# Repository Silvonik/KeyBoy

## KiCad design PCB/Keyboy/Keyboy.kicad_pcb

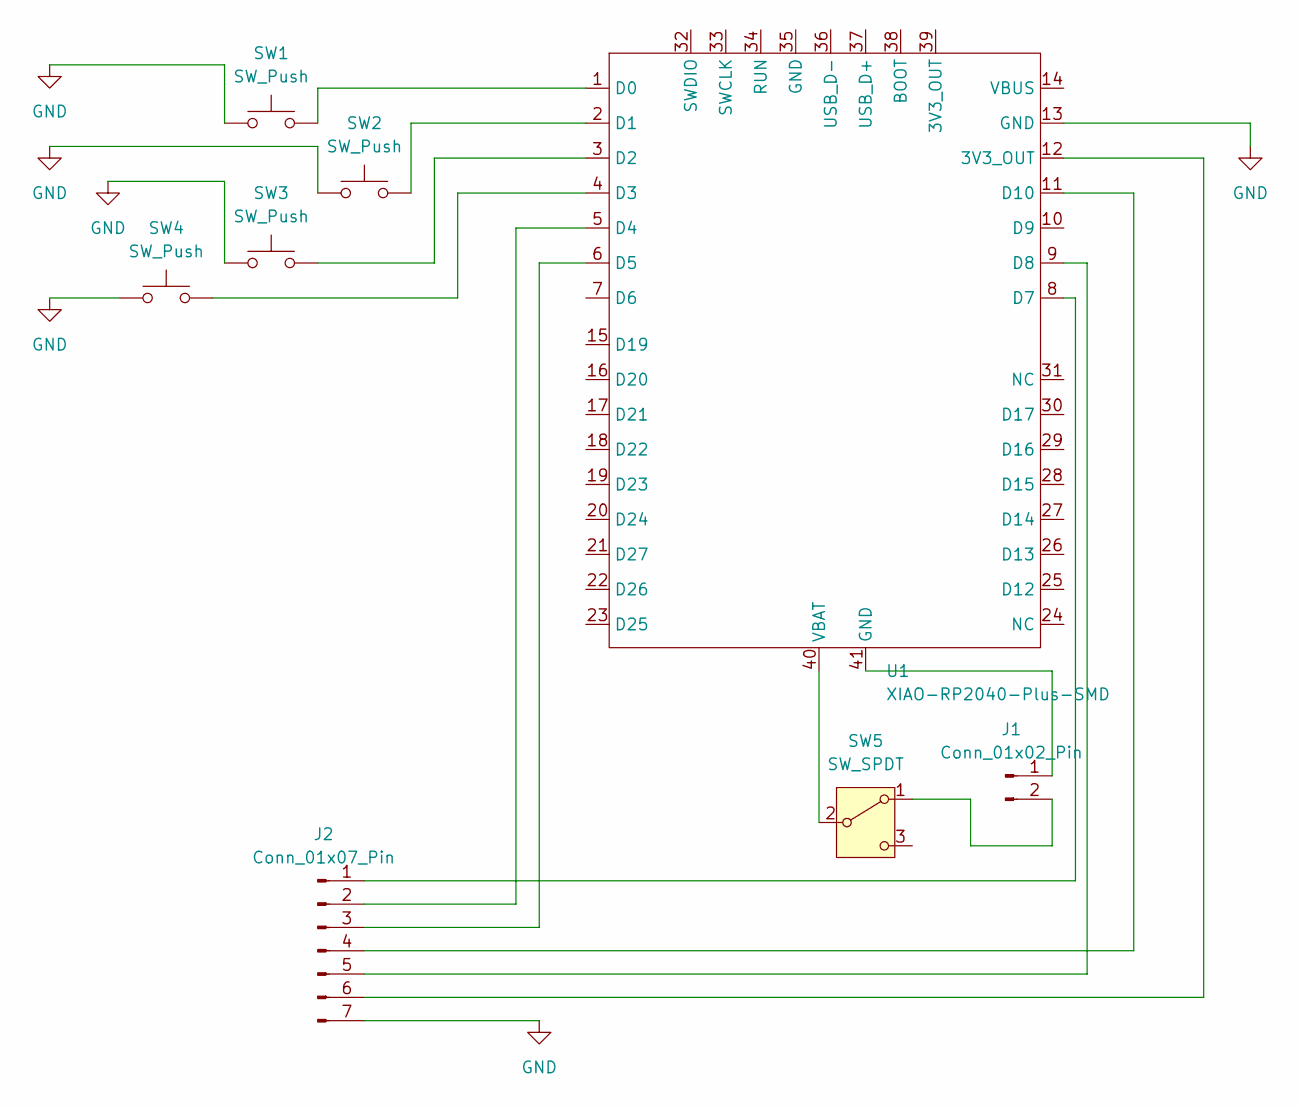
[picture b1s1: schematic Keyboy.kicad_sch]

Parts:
J1: Conn_01x02_Pin; PinHeader_1x02_P2.54mm_Vertical
J2: Conn_01x07_Pin; PinHeader_1x07_P2.54mm_Vertical
SW1, SW2, SW3, SW4: SW_Push; SW_PUSH_6mm
SW5: SW_SPDT; SW_Slide-03_Wuerth-WS-SLTV_10x2.5x6.4_P2.54mm
U1: XIAO-RP2040-Plus-SMD

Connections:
GND: J2.7, SW1.1, SW2.1, SW3.1, SW4.1, U1.13 (GND)
unnamed: J1.1, U1.41 (GND)
unnamed: J1.2, SW5.1 (A)
unnamed: J2.1, U1.8 (D7)
unnamed: J2.2, U1.5 (D4)
unnamed: J2.3, U1.6 (D5)
unnamed: J2.4, U1.11 (D10)
unnamed: J2.5, U1.9 (D8)
unnamed: J2.6, U1.12 (3V3_OUT)
unnamed: SW5.2 (B), U1.40 (VBAT)
unnamed: SW1.2, U1.1 (D0)
unnamed: SW2.2, U1.2 (D1)
unnamed: SW3.2, U1.3 (D2)
unnamed: SW4.2, U1.4 (D3)

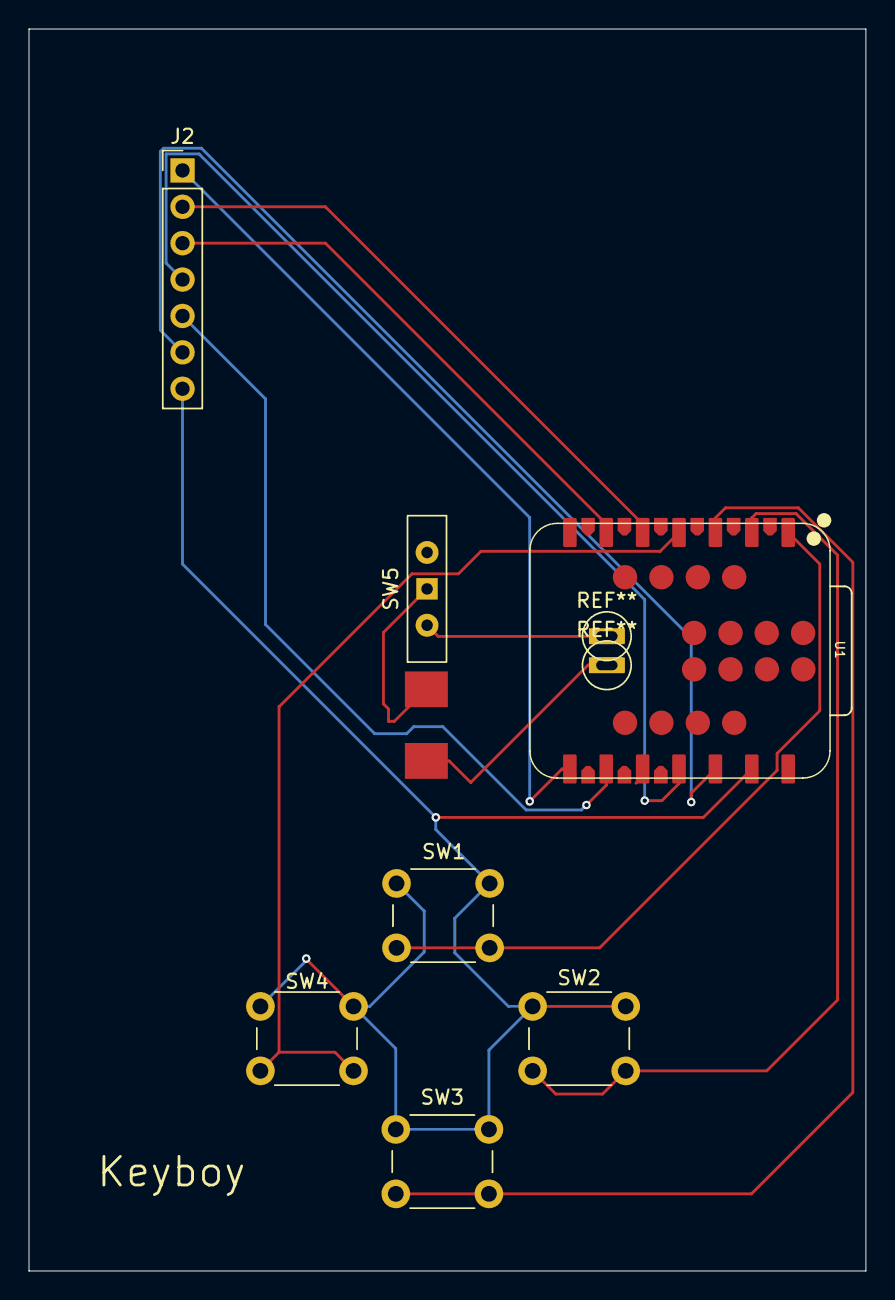
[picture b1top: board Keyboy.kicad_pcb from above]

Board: 2 copper layers, 58.4 x 86.7 mm, 8 parts (1 on the bottom side), 14 nets.
